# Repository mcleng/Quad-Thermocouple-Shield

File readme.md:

Quad Thermocouple Shield
==========================

This work is licensed under a <a rel="license" href="http://creativecommons.org/licenses/by-sa/3.0/">Creative Commons Attribution-ShareAlike 3.0 Unported License</a>.

Designed By:

*	Ryan McLaughlin <ryan@ryanjmclaughlin.com>

Summary
-------

The thermocouple shield was based upon the original breakout board developed for the MAX6675.  While this is a great little chip it is a small surface mount part and therefore difficult to solder. The thermocouple shield helps with having the MAX31855 chip broken out to a simple 0.1" header, a direct interface the the shield, and also provides a PCB Thermocouple Connector to easily interface to a thermocouple. Thermocouple wires are not designed to be soldered and this provides a good solid connection, while also using the proper metals in the connector required for a thermocouple connection.

Connections to Arduino pins are through solder jumpers (normally-closed), however trace is easily cuttable to be able to re-map connections to different pins.  The TXB0106 level shifter to translates 5V Arduino signals to the MAX31855 (3.3V) so the shield can be used with 5V and 3.3V Arduino platforms. Arduino reset switch on the shield.  A secondary set of headers to breakout Arduino pins along sides of the shield to allow for easy prototyping or re-mapping of connections.

Board Specs
-----------

*	Dimensions: Arduino Shield
*	Chip: MAX31855 (4), TXB0106 (1)
*	Voltage: 5V, 3.3V
*	Header: 2 - 1x6 0.1" Pitch, 2 - 1x8 0.1" Pitch
*	Alternate Connection: 2x5 0.1" Pitch header
*	Fixturing: Matching holes to Arduino
*	Pin Connections
	*	13 - SCK
	*	12 - SO
	*	10 - CS1
	*	9 - CS2
	*	8 - CS3
	*	7 - CS4
	*	6 - LED1

Tutorial
--------

It is simple to get everything up and running.

1.	Install a set of shield headers or shield stacking headers to the board
2.	(Optional) Cut solder jumpers if you need to connect the MAX31855 to different pins but adding jumpers between center header and shield pins.
3.	Connect a K-Type [Thermocouple](http://en.wikipedia.org/wiki/Thermocouple Thermocouple)
4.	Load one of the samples from the [[MAX31855 Arduino Library]] and you should see temperature information in the serial console.

Versions
--------

###v2.0

This version changed to the MAX31855 thermocouple chip. Other changes included:

* Initial release under Eagle 6.1 on Github
* Change to MAX31855 chip
* Change solder jumpers to be normally-closed, however trace is easily cuttable
* Added TXB0106 level shifter to translate 5V Arduino signals to the MAX31855
* Updated board dimensions to Adafruit Eagle Library definition
* Updated fixturing holes to follow Arduino fixturing holes
* Added Arduino reset switch
* Added secondary set of headers to breakout Arduino pins along sides of the shield
* Updated prototyping holes to fall on same 0.1" grid as Arduino headers
* PCB production dates 09-2011

####Board Specs
* Dimensions: Arduino Shield
* Chip: MAX31855 (4), TXB0106
* Voltage: 5V, 3.3V
* Header: 2 - 1x6 0.1" Pitch, 2 - 1x8 0.1" Pitch
* Fixturing: Matching holes to Arduino

###Version 1.3

This version made some minor changes based on some feedback of the original version.  The changes included:

* Addition of solder jumpers to allow for disconnection of shield header traces
* The solder mask was not updated on this board and still shows V1.2, however the board is V1.3

####Board Specs
* Dimensions: Arduino Shield
* Chip: 1, 2, or 4 MAX6675
* Header: 2 - 1x6 0.1" Pitch, 2 - 1x8 0.1" Pitch
* Fixturing: Three Corner Holes

###Version 1.2

This board is adapted from the Quad Thermocouple Interface and made to be in a shield format.  It is designed to be able to use 1-4 MAX6675 chips to interface to thermocouples.  One end of the board is left open with 0.1" pitch holes for prototyping space.  Unfortunately due the the height of the thermocouple connectors the shields must be the top shield.

####Board Specs
* Dimensions: Arduino Shield
* Chip: 1, 2, or 4 MAX6675
* Header: 2 - 1x6 0.1" Pitch, 2 - 1x8 0.1" Pitch
* Fixturing: Three Corner Holes

Software
--------

See [[MAX31855 Arduino Library]] for code examples.

Purchase
--------

[store.ryanjmclaughlin.com](http://store.ryanjmclaughlin.com) 

TODO
----

*	Do not route LED through level shifter
*	Add 3.3V connection to center 2x5 header
*	Move reset button further from tc connector

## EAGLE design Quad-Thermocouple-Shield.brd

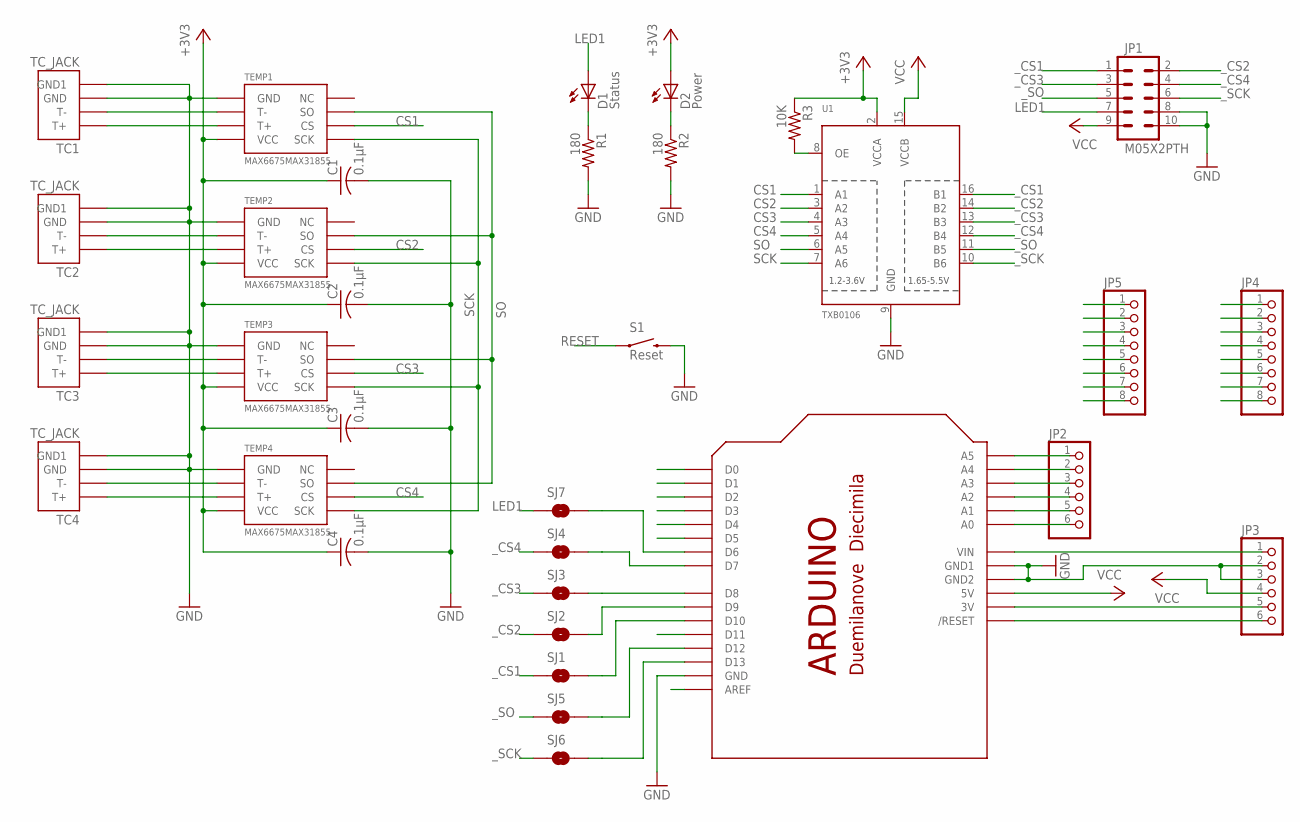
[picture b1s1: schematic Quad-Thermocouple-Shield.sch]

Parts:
C1, C2, C3, C4: 0.1µF; C0603
D1: Status; CHIPLED_0805
D2: Power; CHIPLED_0805
JP1: M05X2PTH; AVR_ICSP
JP2, JP3: PINHD-1X6CB; 1X06-CLEANBIG
JP4, JP5: PINHD-1X8CLEANBIG; 1X08-CLEANBIG
R1, R2: 180; R0603
R3: 10K; R0603
S1: Reset; TACTILE_SWITCH_SMD
SJ1, SJ2, SJ3, SJ4, SJ5, SJ6, SJ7: SOLDERJUMPERTRACE; SJ_2S-TRACE
TC1, TC2, TC3, TC4: TC_JACK
TEMP1, TEMP2, TEMP3, TEMP4: MAX6675MAX31855; SOIC-8
U1: TXB0106; TSSOP16
U$3: ARDUINOUNO; ARDUINO

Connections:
+3V3: C1.1, C2.1, C3.1, C4.1, D2.A, JP3.5, R3.1, TEMP1.VCC, TEMP2.VCC, TEMP3.VCC, TEMP4.VCC, U1.2 (VCCA), U$3.3V
AREF: JP4.8, U$3.AREF
CS1: TEMP1.CS, U1.1 (A1)
CS2: TEMP2.CS, U1.3 (A2)
CS3: TEMP3.CS, U1.4 (A3)
CS4: TEMP4.CS, U1.5 (A4)
D0: JP5.1, U$3.D0
D1: JP5.2, U$3.D1
D2: JP5.3, U$3.D2
D3: JP5.4, U$3.D3
D4: JP5.5, U$3.D4
D5: JP5.6, U$3.D5
D6: JP5.7, SJ7.2, U$3.D6
D7: JP5.8, SJ4.2, U$3.D7
D8: JP4.1, SJ3.2, U$3.D8
D9: JP4.2, SJ2.2, U$3.D9
D10: JP4.3, SJ1.2, U$3.D10
D11: JP4.4, U$3.D11
D12: JP4.5, SJ5.2, U$3.D12
D13: JP4.6, SJ6.2, U$3.D13
GND: C1.2, C2.2, C3.2, C4.2, JP1.8, JP1.10, JP3.2, JP3.3, JP4.7, R1.2, R2.2, S1.3 (2), TC1.P$1 (GND), TC1.P$2 (GND1), TC2.P$1 (GND), TC2.P$2 (GND1), TC3.P$1 (GND), TC3.P$2 (GND1), TC4.P$1 (GND), TC4.P$2 (GND1), TEMP1.GND, TEMP2.GND, TEMP3.GND, TEMP4.GND, U1.9 (GND), U$3.GND, U$3.GND1, U$3.GND2
LED1: D1.A, JP1.7, SJ7.1
unnamed: D1.C, R1.1
unnamed: JP2.1, U$3.A5
unnamed: JP2.2, U$3.A4
unnamed: D2.C, R2.1
unnamed: JP2.3, U$3.A3
unnamed: JP2.4, U$3.A2
unnamed: R3.2, U1.8 (OE)
unnamed: JP2.5, U$3.A1
unnamed: JP2.6, U$3.A0
unnamed: JP3.1, U$3.VIN
RESET: JP3.6, S1.1, U$3.RESET (/RESET)
SCK: TEMP1.SCK, TEMP2.SCK, TEMP3.SCK, TEMP4.SCK, U1.7 (A6)
SO: TEMP1.SO, TEMP2.SO, TEMP3.SO, TEMP4.SO, U1.6 (A5)
T1+: TC1.T+, TEMP1.T+
T1-: TC1.T-, TEMP1.T-
T2+: TC2.T+, TEMP2.T+
T2-: TC2.T-, TEMP2.T-
T3+: TC3.T+, TEMP3.T+
T3-: TC3.T-, TEMP3.T-
T4+: TC4.T+, TEMP4.T+
T4-: TC4.T-, TEMP4.T-
VCC: JP1.9, JP3.4, U1.15 (VCCB), U$3.5V
_CS1: JP1.1, SJ1.1, U1.16 (B1)
_CS2: JP1.2, SJ2.1, U1.14 (B2)
_CS3: JP1.3, SJ3.1, U1.13 (B3)
_CS4: JP1.4, SJ4.1, U1.12 (B4)
_SCK: JP1.6, SJ6.1, U1.10 (B6)
_SO: JP1.5, SJ5.1, U1.11 (B5)

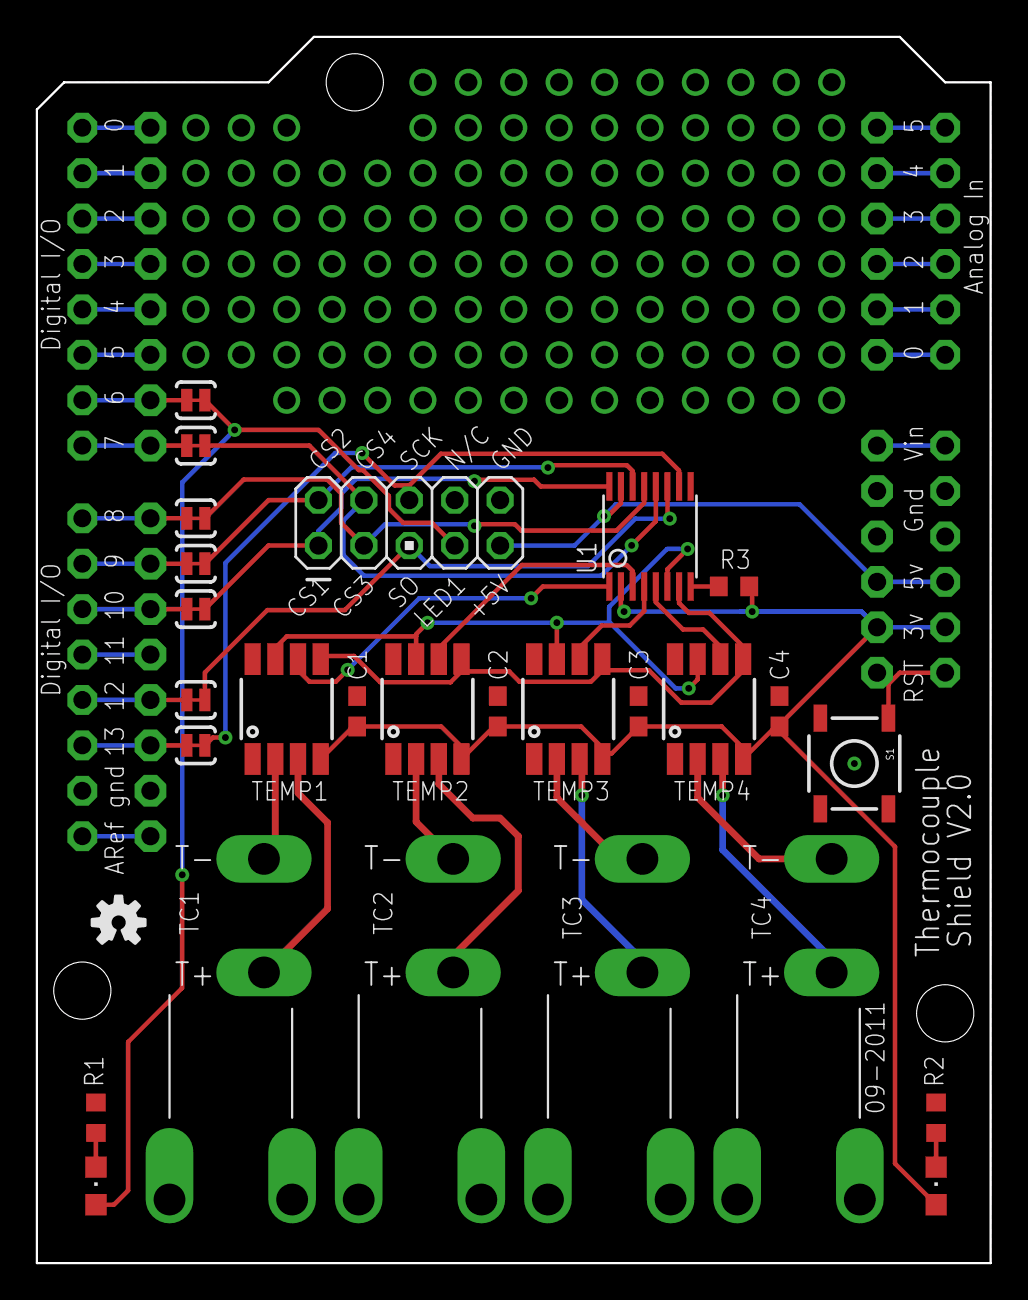
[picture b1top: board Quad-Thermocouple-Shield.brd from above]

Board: 2 copper layers, 53.3 x 68.6 mm, 33 parts (0 on the bottom side), 50 nets.

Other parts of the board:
U$2: OSHW-LOGO-S

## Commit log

2012-01-29 Initial release on github. v2.0

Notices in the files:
readme.md:
CC BY-SA 3.0
